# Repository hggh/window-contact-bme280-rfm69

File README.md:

# window-contact-rfm69

## Parts
 * Atmel 328p
 * RFM69
 * copper foil as contact
 * CR2032 battery

 ## fuse
  * disable BOD
  * internal 1Mhz

the back side of the case. the contacts are made with tiny copper foil.

window is half opened and cover is missing to hide the pcb

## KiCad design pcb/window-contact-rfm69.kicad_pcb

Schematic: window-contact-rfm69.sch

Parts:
BT1: CR2477
C1: 10uF; c_elec_4x5.8
C2, C3: 100nf; C_0805_HandSoldering
D1: RE2
D2: RE1
IC1: ATMEGA328P-A; TQFP-32_7x7mm_Pitch0.8mm
P1: VCC; Wire_SMD_Pad_1PIN
P2: TX/RX; Pin_Header_Straight_1x02
P3: RE1; Wire_SMD_Pad_1PIN
P4: ISP; SMD
P5: RE2; Wire_SMD_Pad_1PIN
P6: AN; SolderWirePad_single_1mmDrill
P7: RE3; Wire_SMD_Pad_1PIN
R1: 10k; R_0805_HandSoldering
R2, R3, R7, R9: 10M; R_0805_HandSoldering
R4, R5, R6: 1k; R_0805_HandSoldering
R8: 100
RF1: RFM69; RFM96
SW1: LED ON

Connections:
/MISO: IC1.16 ((PCINT4/MISO)PB4), P4.1, R4.2
/MOSI: IC1.15 ((PCINT3/OC2A/MOSI)PB3), P4.4, R6.1
/SCK: IC1.17 ((PCINT5/SCK)PB5), P4.3, R5.1
/SS: IC1.14 ((PCINT2/OC1B/~SS~)PB2), RF1.7 (NSS)
GND: BT1.2 (-), C1.2, C2.2, C3.2, IC1.3 (GND), IC1.5 (GND), IC1.21 (GND), P4.6, R2.2, R3.2, R7.2, R8.1, R9.2, RF1.3 (GND), RF1.14 (GND)
unnamed: D1.1 (K), D2.1 (K), R8.2
unnamed: D1.2 (A), IC1.8 ((PCINT7/XTAL2/TOSC2)PB7)
unnamed: D2.2 (A), IC1.7 ((PCINT6/XTAL1/TOSC1)PB6)
unnamed: IC1.1 ((PCINT19/OC2B/INT1)PD3), R9.1, SW1.1
unnamed: IC1.23 ((PCINT8/ADC0)PC0), P5.1, R3.1
unnamed: IC1.24 ((PCINT9/ADC1)PC1), P3.1, R2.1
unnamed: IC1.25 ((PCINT10/ADC2)PC2), P7.1, R7.1
unnamed: IC1.29 ((PCINT14/~RESET~)PC6), P4.5, R1.2
unnamed: IC1.30 ((PCINT16/RXD)PD0), P2.1
unnamed: IC1.31 ((PCINT17/TXD)PD1), P2.2
unnamed: IC1.32 ((PCINT18/INT0)PD2), RF1.9 (DIO0)
unnamed 28: P6.1, RF1.1 (ANT); also elsewhere on the board
unnamed: R4.1, RF1.8 (MISO)
unnamed: R5.2, RF1.6 (SCK)
unnamed: R6.2, RF1.5 (MOSI)
VCC: BT1.1 (+), C1.1, C2.1, C3.1, IC1.4 (VCC), IC1.6 (VCC), IC1.18 (AVCC), P1.1, P4.2, R1.1, RF1.2 (VCC_3.3V), SW1.2

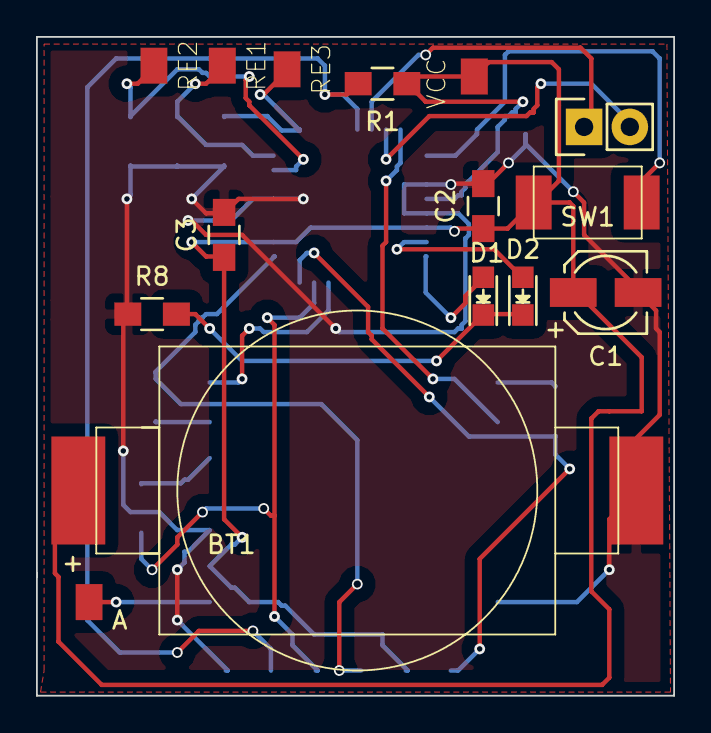
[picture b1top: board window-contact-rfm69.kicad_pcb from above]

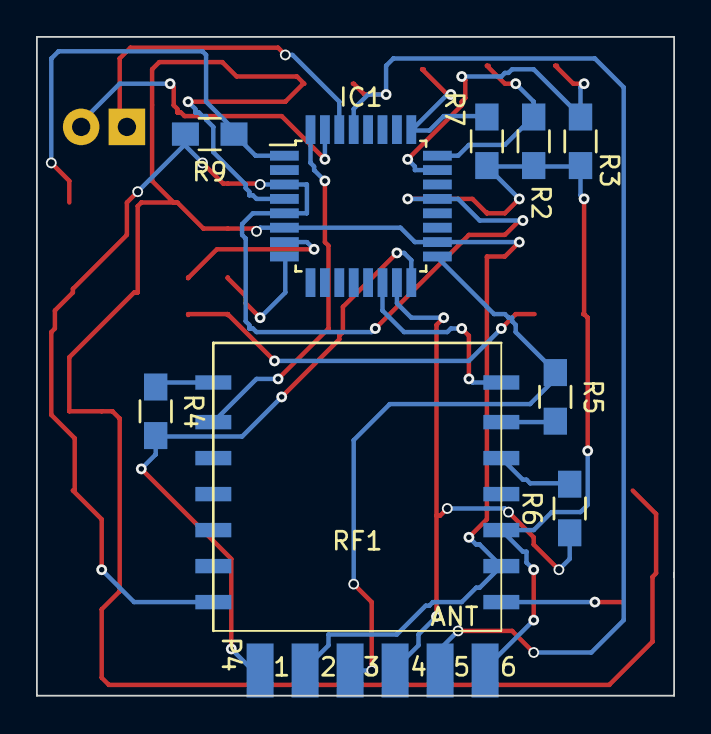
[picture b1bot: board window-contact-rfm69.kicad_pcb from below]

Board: 2 copper layers, 35.4 x 36.6 mm, 25 parts (10 on the bottom side), 21 nets.

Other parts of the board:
A: AN; Wire_SMD_Pad_1PIN

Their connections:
unnamed 28: A.1; also elsewhere on the board

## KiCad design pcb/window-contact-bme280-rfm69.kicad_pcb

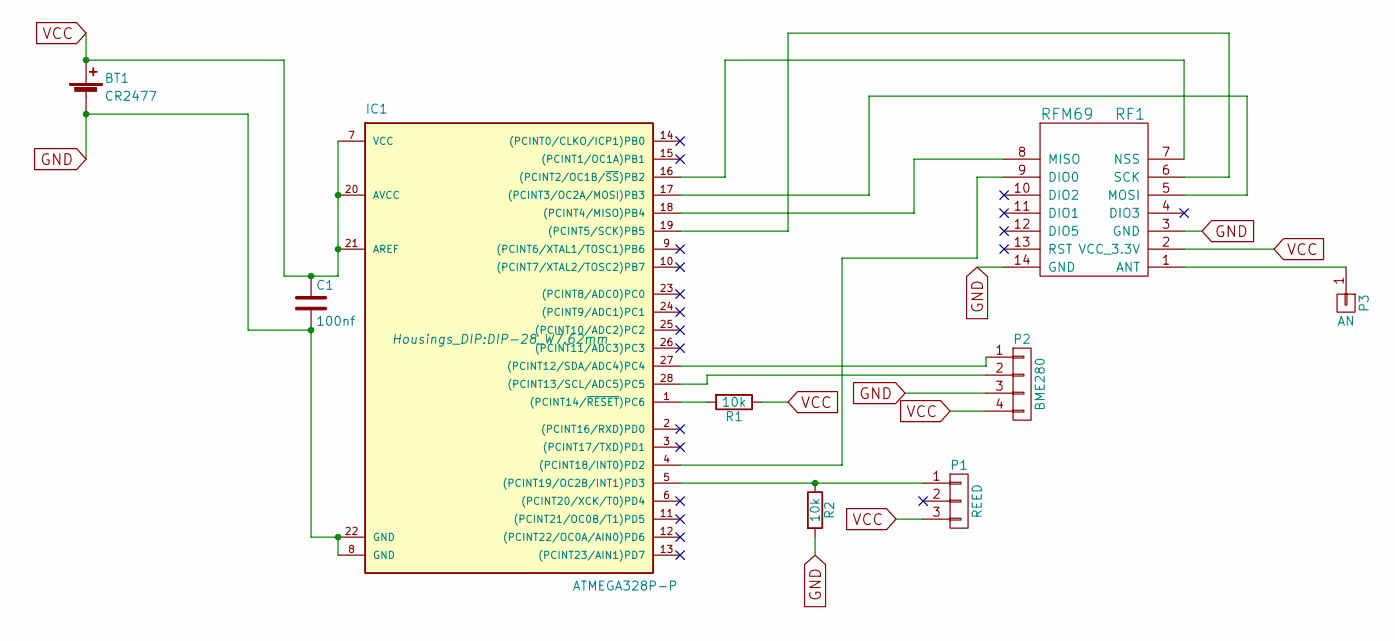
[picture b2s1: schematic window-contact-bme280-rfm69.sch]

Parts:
BT1: CR2477
C1: 100nf; C_0805_HandSoldering
IC1: ATMEGA328P-P; DIP-28_W7.62mm
P1: REED; Pin_Header_Straight_1x03
P2: BME280; Pin_Header_Straight_1x04
P3: AN; SolderWirePad_single_1mmDrill
R1, R2: 10k; R_0805_HandSoldering
RF1: RFM69; RFM96

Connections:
GND: BT1.2 (-), C1.2, IC1.8 (GND), IC1.22 (GND), P2.3, R2.2, RF1.3 (GND), RF1.14 (GND)
unnamed: IC1.1 ((PCINT14/~RESET~)PC6), R1.2
unnamed: IC1.4 ((PCINT18/INT0)PD2), RF1.9 (DIO0)
unnamed: IC1.5 ((PCINT19/OC2B/INT1)PD3), P1.1, R2.1
unnamed: IC1.16 ((PCINT2/OC1B/~SS~)PB2), RF1.7 (NSS)
unnamed: IC1.17 ((PCINT3/OC2A/MOSI)PB3), RF1.5 (MOSI)
unnamed: IC1.18 ((PCINT4/MISO)PB4), RF1.8 (MISO)
unnamed: IC1.19 ((PCINT5/SCK)PB5), RF1.6 (SCK)
unnamed: IC1.27 ((PCINT12/SDA/ADC4)PC4), P2.1
unnamed: IC1.28 ((PCINT13/SCL/ADC5)PC5), P2.2
unnamed: P3.1, RF1.1 (ANT)
VCC: BT1.1 (+), C1.1, IC1.7 (VCC), IC1.20 (AVCC), IC1.21 (AREF), P1.3, P2.4, R1.1, RF1.2 (VCC_3.3V)

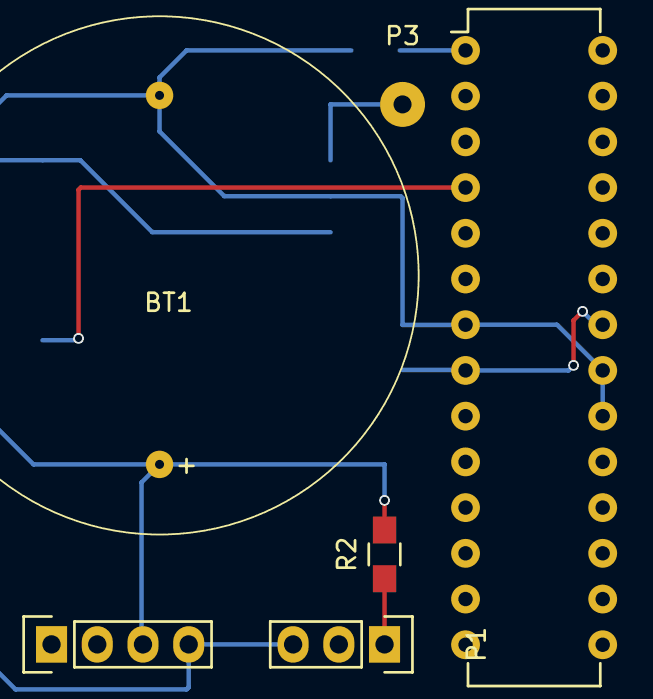
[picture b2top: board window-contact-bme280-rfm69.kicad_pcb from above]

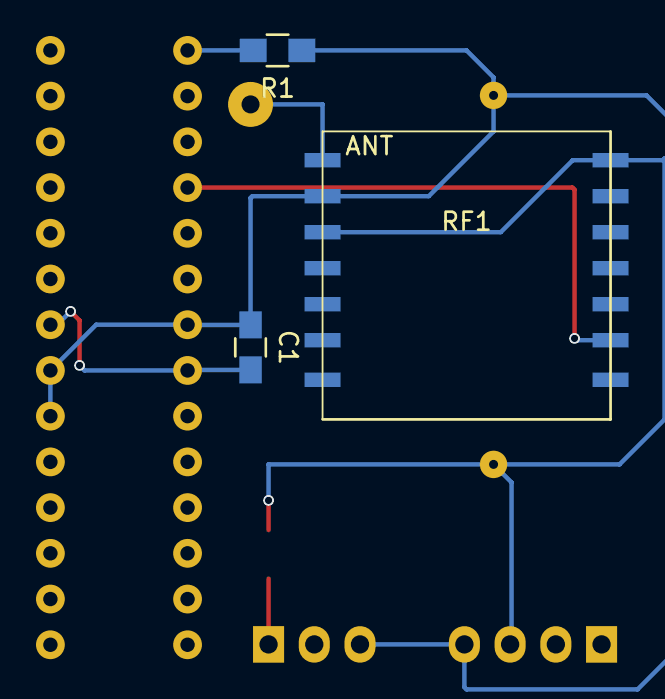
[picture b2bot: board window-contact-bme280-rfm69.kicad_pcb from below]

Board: 2 copper layers, 9 parts (3 on the bottom side), 12 nets.

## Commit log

2018-05-20 add ideas
2018-05-20 initial pcb
2018-05-27 PlatformIO Tests with custom board: BOD disabeled, 1Mhz
2018-05-30 only window contact. to one stuff correct
2018-05-30 only window contact
2018-05-30 switched to usbasp
2018-05-31 added drawing
2018-06-03 read battery voltage via internal 1.1V reference
2018-06-03 changed to tqfp atmel
2018-06-10 updated kicad files
2018-06-10 updated pcb
2018-06-14 update code
2018-06-15 updated svg
2018-06-16 changed to ifdef and int; correct disable of PCINT
2018-06-16 added scad file
2018-06-16 changed to config.h
2018-08-25 updated to different reed contacts
2018-08-25 added openhab2 example config
2018-08-30 added new case, removed old inlay
2018-08-30 3 => 3.5mm hoch; more space for reed contacts
2018-08-31 updated case
2018-08-31 renamed, addd stl
2018-08-31 not needed anymore
2018-08-31 remove newlines
2018-08-31 added Status LEDs and Debug Push Button
2018-08-31 update to new case and reed contacts
2018-09-06 added 3. reed contact
2018-11-23 new release of pcb for window four state contact
2018-11-23 finial version for allpcb
2018-11-23 allpcb order
2018-11-23 added libs via pio dependency manager
2018-11-23 added case for pcb
2018-11-29 update stl added correct odering of difference
2018-12-23 wip: buttons leds
2018-12-23 format
2018-12-27 test with no reed contacts
2018-12-27 updated case: now using contact with copper foil tape
2018-12-28 added plase to fit lid
2018-12-28 update case
2018-12-29 switch to Voltage lib updated logic
2018-12-30 added option for left or right handle
2018-12-30 added pics
2018-12-30 updated to OpenHab QuantityType
2018-12-30 added lid
2019-02-10 if send was successful, blink green
2019-11-19 added new case for reed contact version
2019-12-30 update case for reed contacts
2019-12-30 update for platformIO
2019-12-30 update for reed contacts
2019-12-31 update reed contact case
